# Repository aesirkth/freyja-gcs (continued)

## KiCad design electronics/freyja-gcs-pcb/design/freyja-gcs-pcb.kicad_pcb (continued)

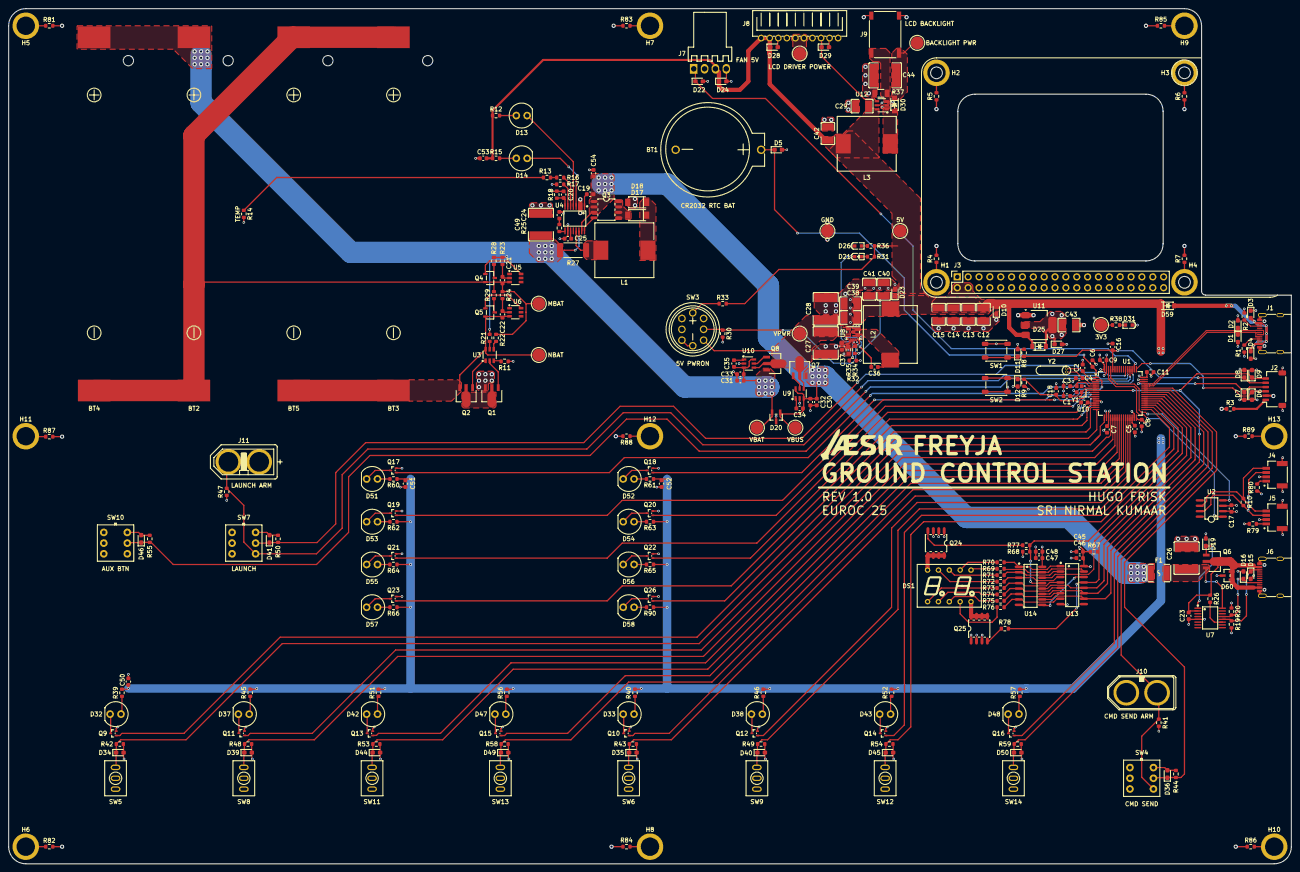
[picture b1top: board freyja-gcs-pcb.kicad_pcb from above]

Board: 4 copper layers, 300.0 x 200.0 mm, 306 parts (1 on the bottom side), 187 nets.

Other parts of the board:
LOGO1: LOGO; aesir_logo_large
LOGO2: LOGO; euroc_logo

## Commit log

2025-05-01 tvs diodes
2025-05-01 add system diagram
2025-05-01 impartGUI tip
2025-05-01 add part selection tip
2025-05-01 todo: buzzer and alarms
2025-05-01 add usb diff directive
2025-05-02 Update README.md
    Included the required number of valve toggle switches
2025-05-02 Update README.md
    Added information about the circuit regarding power and switches.
    Also included is the parts list from LCSC for reference.
2025-05-02 Update README.md
    Updated order
2025-05-09 software spec
2025-05-16 Update README.md
    Changed the part number for the push button (big one!!)
2025-05-16 Update README.md
    Added resistor
2025-05-16 push switch part number
2025-05-16 Added switches and LEDs for the GCB.
2025-05-16 add to todo
2025-06-06 Added FDCAN interface. Connector has to be added!!
2025-07-18 add power circuit
2025-07-18 reset annotation
2025-07-18 fix library
2025-07-18 power: add leds
2025-07-18 power: add 3.3V reg
2025-07-18 fix stub
2025-07-18 add power switch
2025-07-19 add led backlight driver
2025-07-19 fan connector
2025-07-20 increase allowed battery temp
2025-07-20 7 segment display
2025-07-20 edit todo
2025-07-20 global reset
2025-07-20 fix cr2032 short circuit
2025-07-20 change pwm channels
2025-07-20 add can connectors
2025-07-21 buttons and indicators
2025-07-21 more esd diodes
2025-07-21 more esd diodes!
2025-07-23 raspberry pi header
2025-07-23 reset designators
2025-07-23 add jumpers so that can power on cna port can be disconnected
2025-07-23 footprint and lcsc part for all components
2025-07-23 rules and stackup
2025-07-23 3d model improvement
2025-07-24 Updated PCB layout and grouped components
2025-07-25 PCB rough design layout - COMPLETED
2025-07-25 Updated edge cuts, added holes, curved edges, rearranged LEDs, moved battries to top, changed the power delivery USB to right side.
2025-07-25 Updated schematic with the board mounting
2025-07-28 power layout wip
2025-07-30 locked position of components
2025-07-31 mcu layout
2025-08-02 usb pd layout
2025-08-02 charging circuit layout wip
2025-08-03 btn routing wip
2025-08-03 restore SY8368 footprint
2025-08-03 all routed, fine tuning left
2025-08-03 cleanup
2025-08-05 aesir logo
2025-08-05 annotation and pinouts
2025-08-05 remove backups
2025-08-05 fix footprints
2025-08-06 venv with kibot
2025-08-06 pin python version
2025-08-06 dnp logos
2025-08-11 change to available parts
2025-08-11 adjust usb spacing
2025-08-16 correct shunt part numbers
